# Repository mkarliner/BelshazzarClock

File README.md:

# Belshazzar Luminous Night Clock

Here are the files for the PCB, micropython code and STL files for Belshazzar's Clock.
Refer to the KiCad files for the PCB details and BOM for details of compononents, but they
are basically WS2811 SOT8 led drivers, 0805 SMD UV leds and a a small number of resistors and
caps, also 0805 SMD.

There are four 3D printed parts, which are small enough to print on most printers.

You will additionally need -

- Stepper Motor 28BYJ-48 with ULN2003 Driver Board
- 200mm of 100mm ID plastic ducting pipe.
- White paint or paper to cover the pipe
- Glow in the dark paint
- ESP32C3 Super Mini dev board

  I've left a space for a 74AHCT125 level converter to boost the 3.3V logic of the ESP32 to 5V for the WS2811, but on my board at least, it works fine without, you can just jumper over the in and out pins on the level converter.

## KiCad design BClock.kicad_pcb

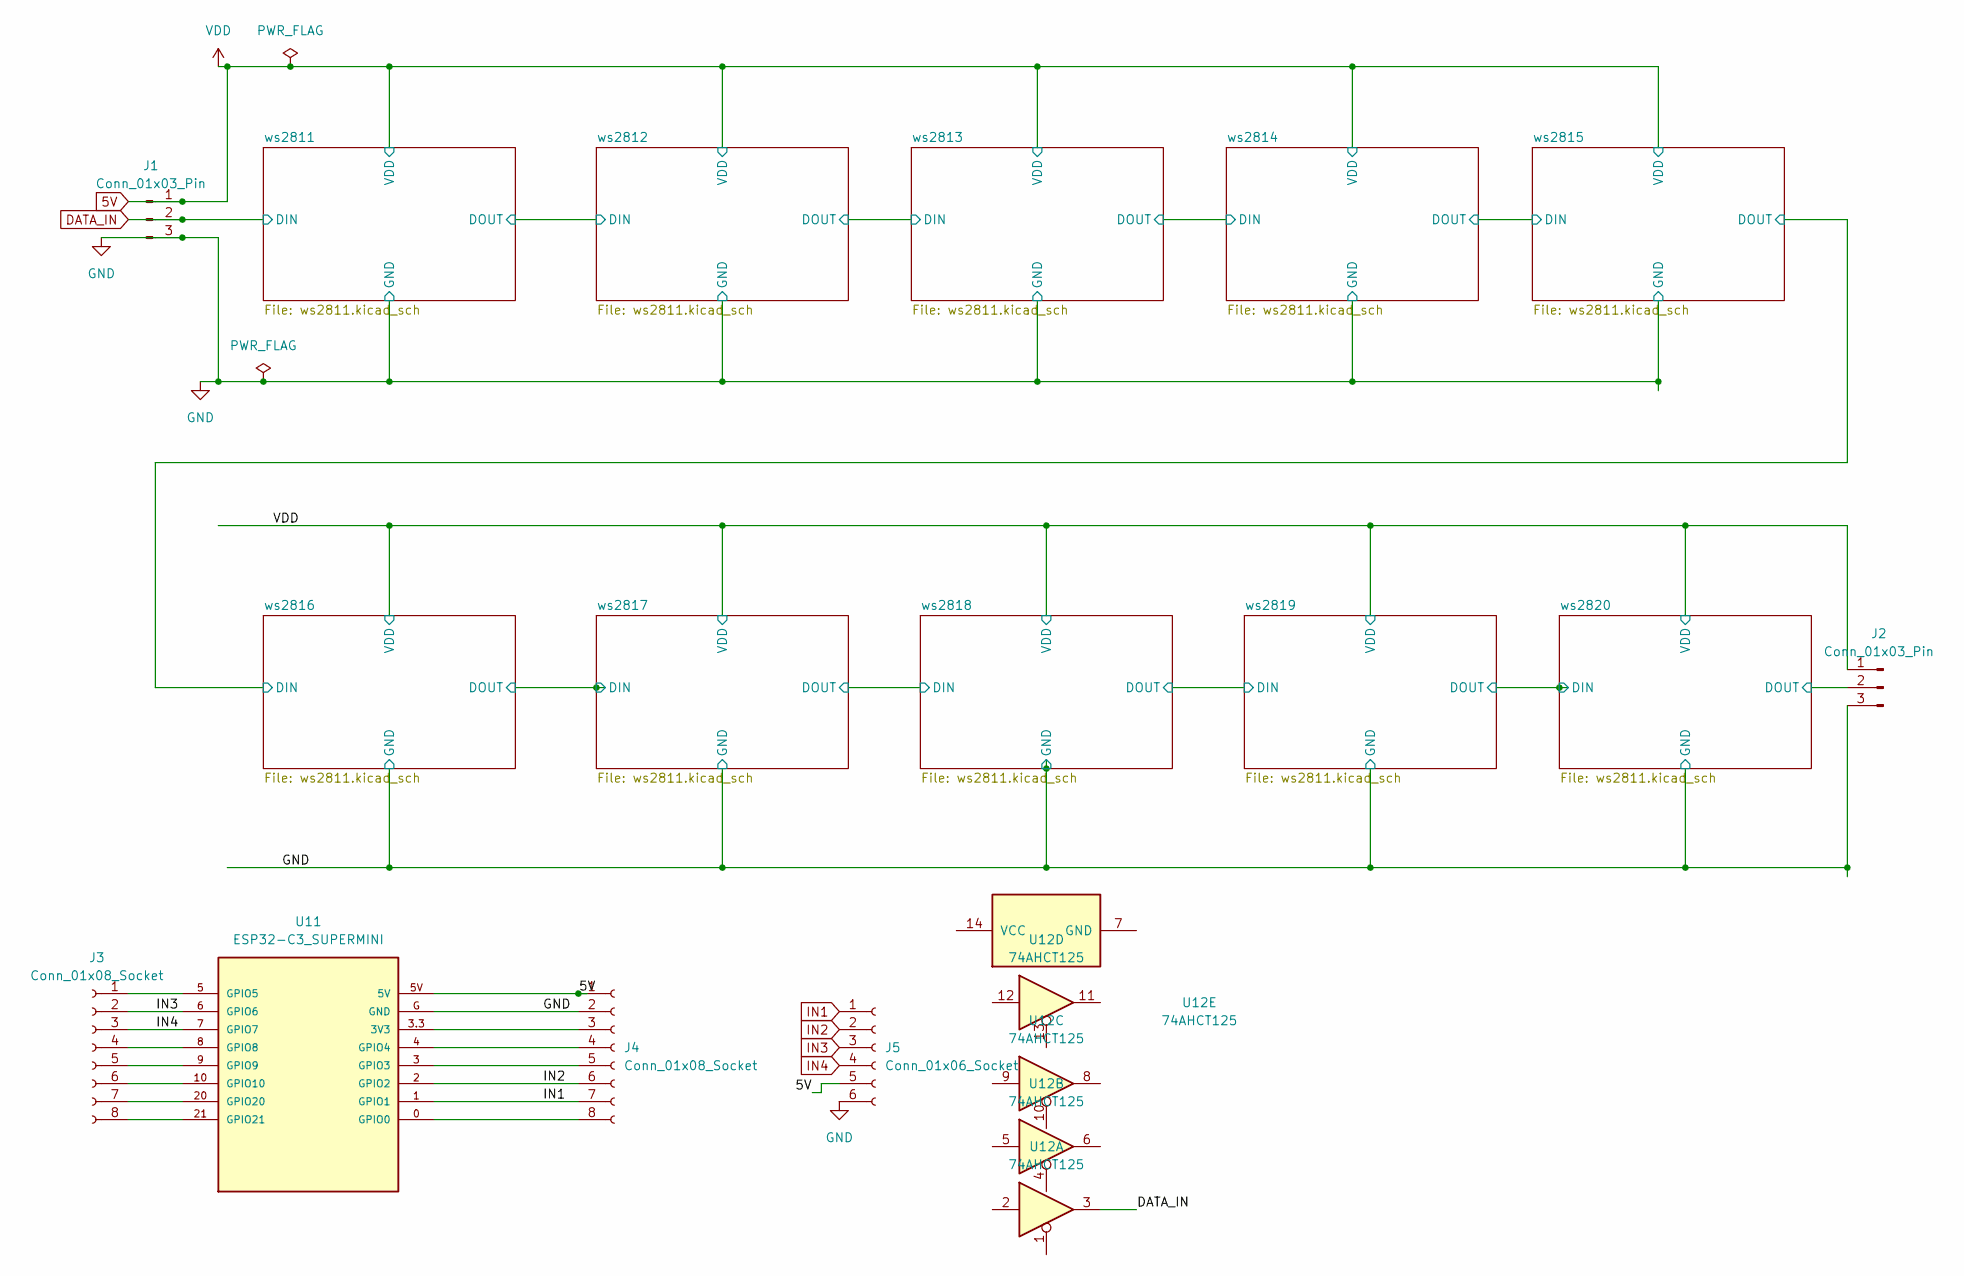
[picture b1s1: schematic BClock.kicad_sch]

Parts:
J1, J2: Conn_01x03_Pin; PinHeader_1x03_P2.54mm_Vertical
J3, J4: Conn_01x08_Socket; PinHeader_1x08_P2.54mm_Vertical
J5: Conn_01x06_Socket; PinHeader_1x06_P2.54mm_Vertical
U11: ESP32-C3_SUPERMINI; MODULE_ESP32-C3_SUPERMINI
U12: 74AHCT125; DIP-14_W10.16mm

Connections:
5V: J1.1, J2.1, J4.1, J5.5, U11.5V; also elsewhere on the board
/ws2820/DOUT: J2.2; also elsewhere on the board
DATA_IN: J1.2, U12.3; also elsewhere on the board
GND: J1.3, J2.3, J4.2, J5.6, U11.G (GND); also elsewhere on the board
IN1: J4.7, J5.1, U11.1 (GPIO1)
IN2: J4.6, J5.2, U11.2 (GPIO2)
IN3: J3.2, J5.3, U11.6 (GPIO6)
IN4: J3.3, J5.4, U11.7 (GPIO7)
unnamed: J3.1, U11.5 (GPIO5)
unnamed: J3.4, U11.8 (GPIO8)
unnamed: J3.5, U11.9 (GPIO9)
unnamed: J3.6, U11.10 (GPIO10)
unnamed: J3.7, U11.20 (GPIO20)
unnamed: J3.8, U11.21 (GPIO21)
unnamed: J4.3, U11.3.3 (3V3)
unnamed: J4.4, U11.4 (GPIO4)
unnamed: J4.5, U11.3 (GPIO3)
unnamed: J4.8, U11.0 (GPIO0)

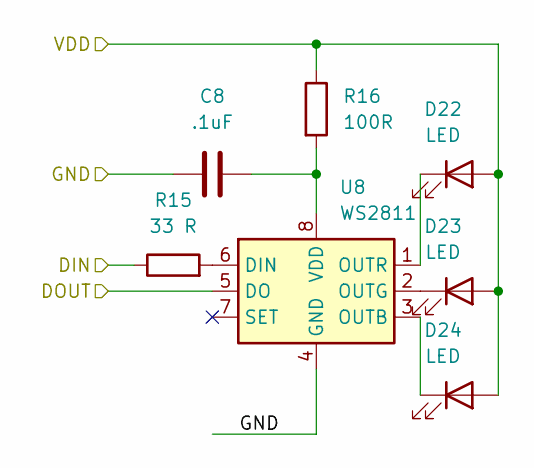
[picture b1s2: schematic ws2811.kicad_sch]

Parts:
C8: .1uF; C_0805_2012Metric
D22, D23, D24: LED; LED_0805_2012Metric
R15: 33 R; R_0805_2012Metric
R16: 100R; R_0805_2012Metric
U8: WS2811; SOP-8_3.9x4.9mm_P1.27mm

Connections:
5V: D22.2 (A), D23.2 (A), D24.2 (A), R16.1; also elsewhere on the board
/ws2817/DOUT: R15.1; also elsewhere on the board
/ws2818/DOUT: U8.5 (DO); also elsewhere on the board
GND: C8.1, U8.4 (GND); also elsewhere on the board
unnamed: D22.1 (K), U8.1 (OUTR)
unnamed: D23.1 (K), U8.2 (OUTG)
unnamed: D24.1 (K), U8.3 (OUTB)
unnamed: R15.2, U8.6 (DIN)
unnamed: C8.2, R16.2, U8.8 (VDD)

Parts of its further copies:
C1, C2, C3, C4, C5, C6, C7, C9, C10: .1uF; C_0805_2012Metric
D1, D2, D3, D4, D5, D6, D7, D8, D9, D10, D11, D12, D13, D14, D15, D16, D17, D18, D19, D20, D21, D25, D26, D27, D28, D29, D30: LED; LED_0805_2012Metric
R1, R3, R5, R7, R9, R11, R13, R17, R19: 33 R; R_0805_2012Metric
R2, R4, R6, R8, R10, R12, R14, R18, R20: 100R; R_0805_2012Metric
U1, U2, U3, U4, U5, U6, U7, U9, U10: WS2811; SOP-8_3.9x4.9mm_P1.27mm

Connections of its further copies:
5V: D1.2 (A), D2.2 (A), D3.2 (A), D4.2 (A), D5.2 (A), D6.2 (A), D7.2 (A), D8.2 (A), D9.2 (A), D10.2 (A), D11.2 (A), D12.2 (A), D13.2 (A), D14.2 (A), D15.2 (A), D16.2 (A), D17.2 (A), D18.2 (A), D19.2 (A), D20.2 (A), D21.2 (A), D25.2 (A), D26.2 (A), D27.2 (A), D28.2 (A), D29.2 (A), D30.2 (A), R2.1, R4.1, R6.1, R8.1, R10.1, R12.1, R14.1, R18.1, R20.1; also elsewhere on the board
/ws2811/DOUT: R3.1, U1.5 (DO)
/ws2812/DOUT: R5.1, U2.5 (DO)
/ws2813/DOUT: R7.1, U3.5 (DO)
/ws2814/DOUT: R9.1, U4.5 (DO)
/ws2815/DOUT: R11.1, U5.5 (DO)
/ws2816/DOUT: R13.1, U6.5 (DO)
/ws2817/DOUT: U7.5 (DO); also elsewhere on the board
/ws2818/DOUT: R17.1; also elsewhere on the board
/ws2819/DOUT: R19.1, U9.5 (DO)
/ws2820/DOUT: U10.5 (DO); also elsewhere on the board
DATA_IN: R1.1; also elsewhere on the board
GND: C1.1, C2.1, C3.1, C4.1, C5.1, C6.1, C7.1, C9.1, C10.1, U1.4 (GND), U2.4 (GND), U3.4 (GND), U4.4 (GND), U5.4 (GND), U6.4 (GND), U7.4 (GND), U9.4 (GND), U10.4 (GND); also elsewhere on the board
unnamed: D1.1 (K), U1.1 (OUTR)
unnamed: D2.1 (K), U1.2 (OUTG)
unnamed: D3.1 (K), U1.3 (OUTB)
unnamed: D4.1 (K), U2.1 (OUTR)
unnamed: D5.1 (K), U2.2 (OUTG)
unnamed: D6.1 (K), U2.3 (OUTB)
unnamed: D7.1 (K), U3.1 (OUTR)
unnamed: D8.1 (K), U3.2 (OUTG)
unnamed: D9.1 (K), U3.3 (OUTB)
unnamed: D10.1 (K), U4.1 (OUTR)
unnamed: D11.1 (K), U4.2 (OUTG)
unnamed: D12.1 (K), U4.3 (OUTB)
unnamed: D13.1 (K), U5.1 (OUTR)
unnamed: D14.1 (K), U5.2 (OUTG)
unnamed: D15.1 (K), U5.3 (OUTB)
unnamed: D16.1 (K), U6.1 (OUTR)
unnamed: D17.1 (K), U6.2 (OUTG)
unnamed: D18.1 (K), U6.3 (OUTB)
unnamed: D19.1 (K), U7.1 (OUTR)
unnamed: D20.1 (K), U7.2 (OUTG)
unnamed: D21.1 (K), U7.3 (OUTB)
unnamed: D25.1 (K), U9.1 (OUTR)
unnamed: D26.1 (K), U9.2 (OUTG)
unnamed: D27.1 (K), U9.3 (OUTB)
unnamed: D28.1 (K), U10.1 (OUTR)
unnamed: D29.1 (K), U10.2 (OUTG)
unnamed: D30.1 (K), U10.3 (OUTB)
unnamed: R1.2, U1.6 (DIN)
unnamed: C1.2, R2.2, U1.8 (VDD)
unnamed: R3.2, U2.6 (DIN)
unnamed: C2.2, R4.2, U2.8 (VDD)
unnamed: R5.2, U3.6 (DIN)
unnamed: C3.2, R6.2, U3.8 (VDD)
unnamed: R7.2, U4.6 (DIN)
unnamed: C4.2, R8.2, U4.8 (VDD)
unnamed: R9.2, U5.6 (DIN)
unnamed: C5.2, R10.2, U5.8 (VDD)
unnamed: R11.2, U6.6 (DIN)
unnamed: C6.2, R12.2, U6.8 (VDD)
unnamed: R13.2, U7.6 (DIN)
unnamed: C7.2, R14.2, U7.8 (VDD)
unnamed: R17.2, U9.6 (DIN)
unnamed: C9.2, R18.2, U9.8 (VDD)
unnamed: R19.2, U10.6 (DIN)
unnamed: C10.2, R20.2, U10.8 (VDD)

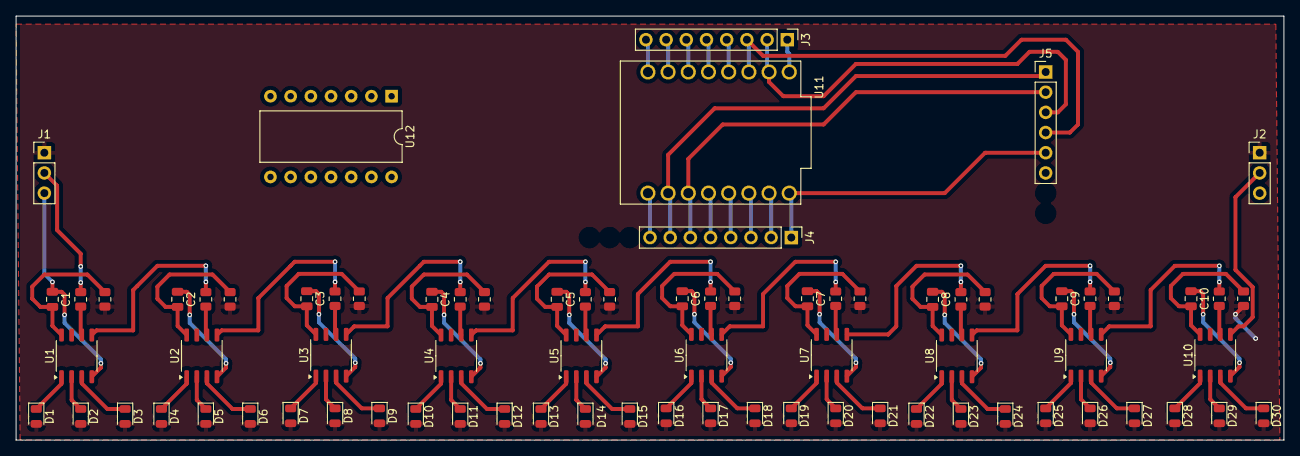
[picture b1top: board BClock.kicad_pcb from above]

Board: 2 copper layers, 159.5 x 53.3 mm, 77 parts (0 on the bottom side), 77 nets.

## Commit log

2024-06-20 NEW: First commit
2024-07-07 NEW: Added ESP32C3 and level shifter
2025-01-07 CHANGE: Unified repo with electronics and source code
2025-01-07 CHANGE: Remove old code, do quarter turn each minute
2025-01-07 ADD: STL files for 3D printing
